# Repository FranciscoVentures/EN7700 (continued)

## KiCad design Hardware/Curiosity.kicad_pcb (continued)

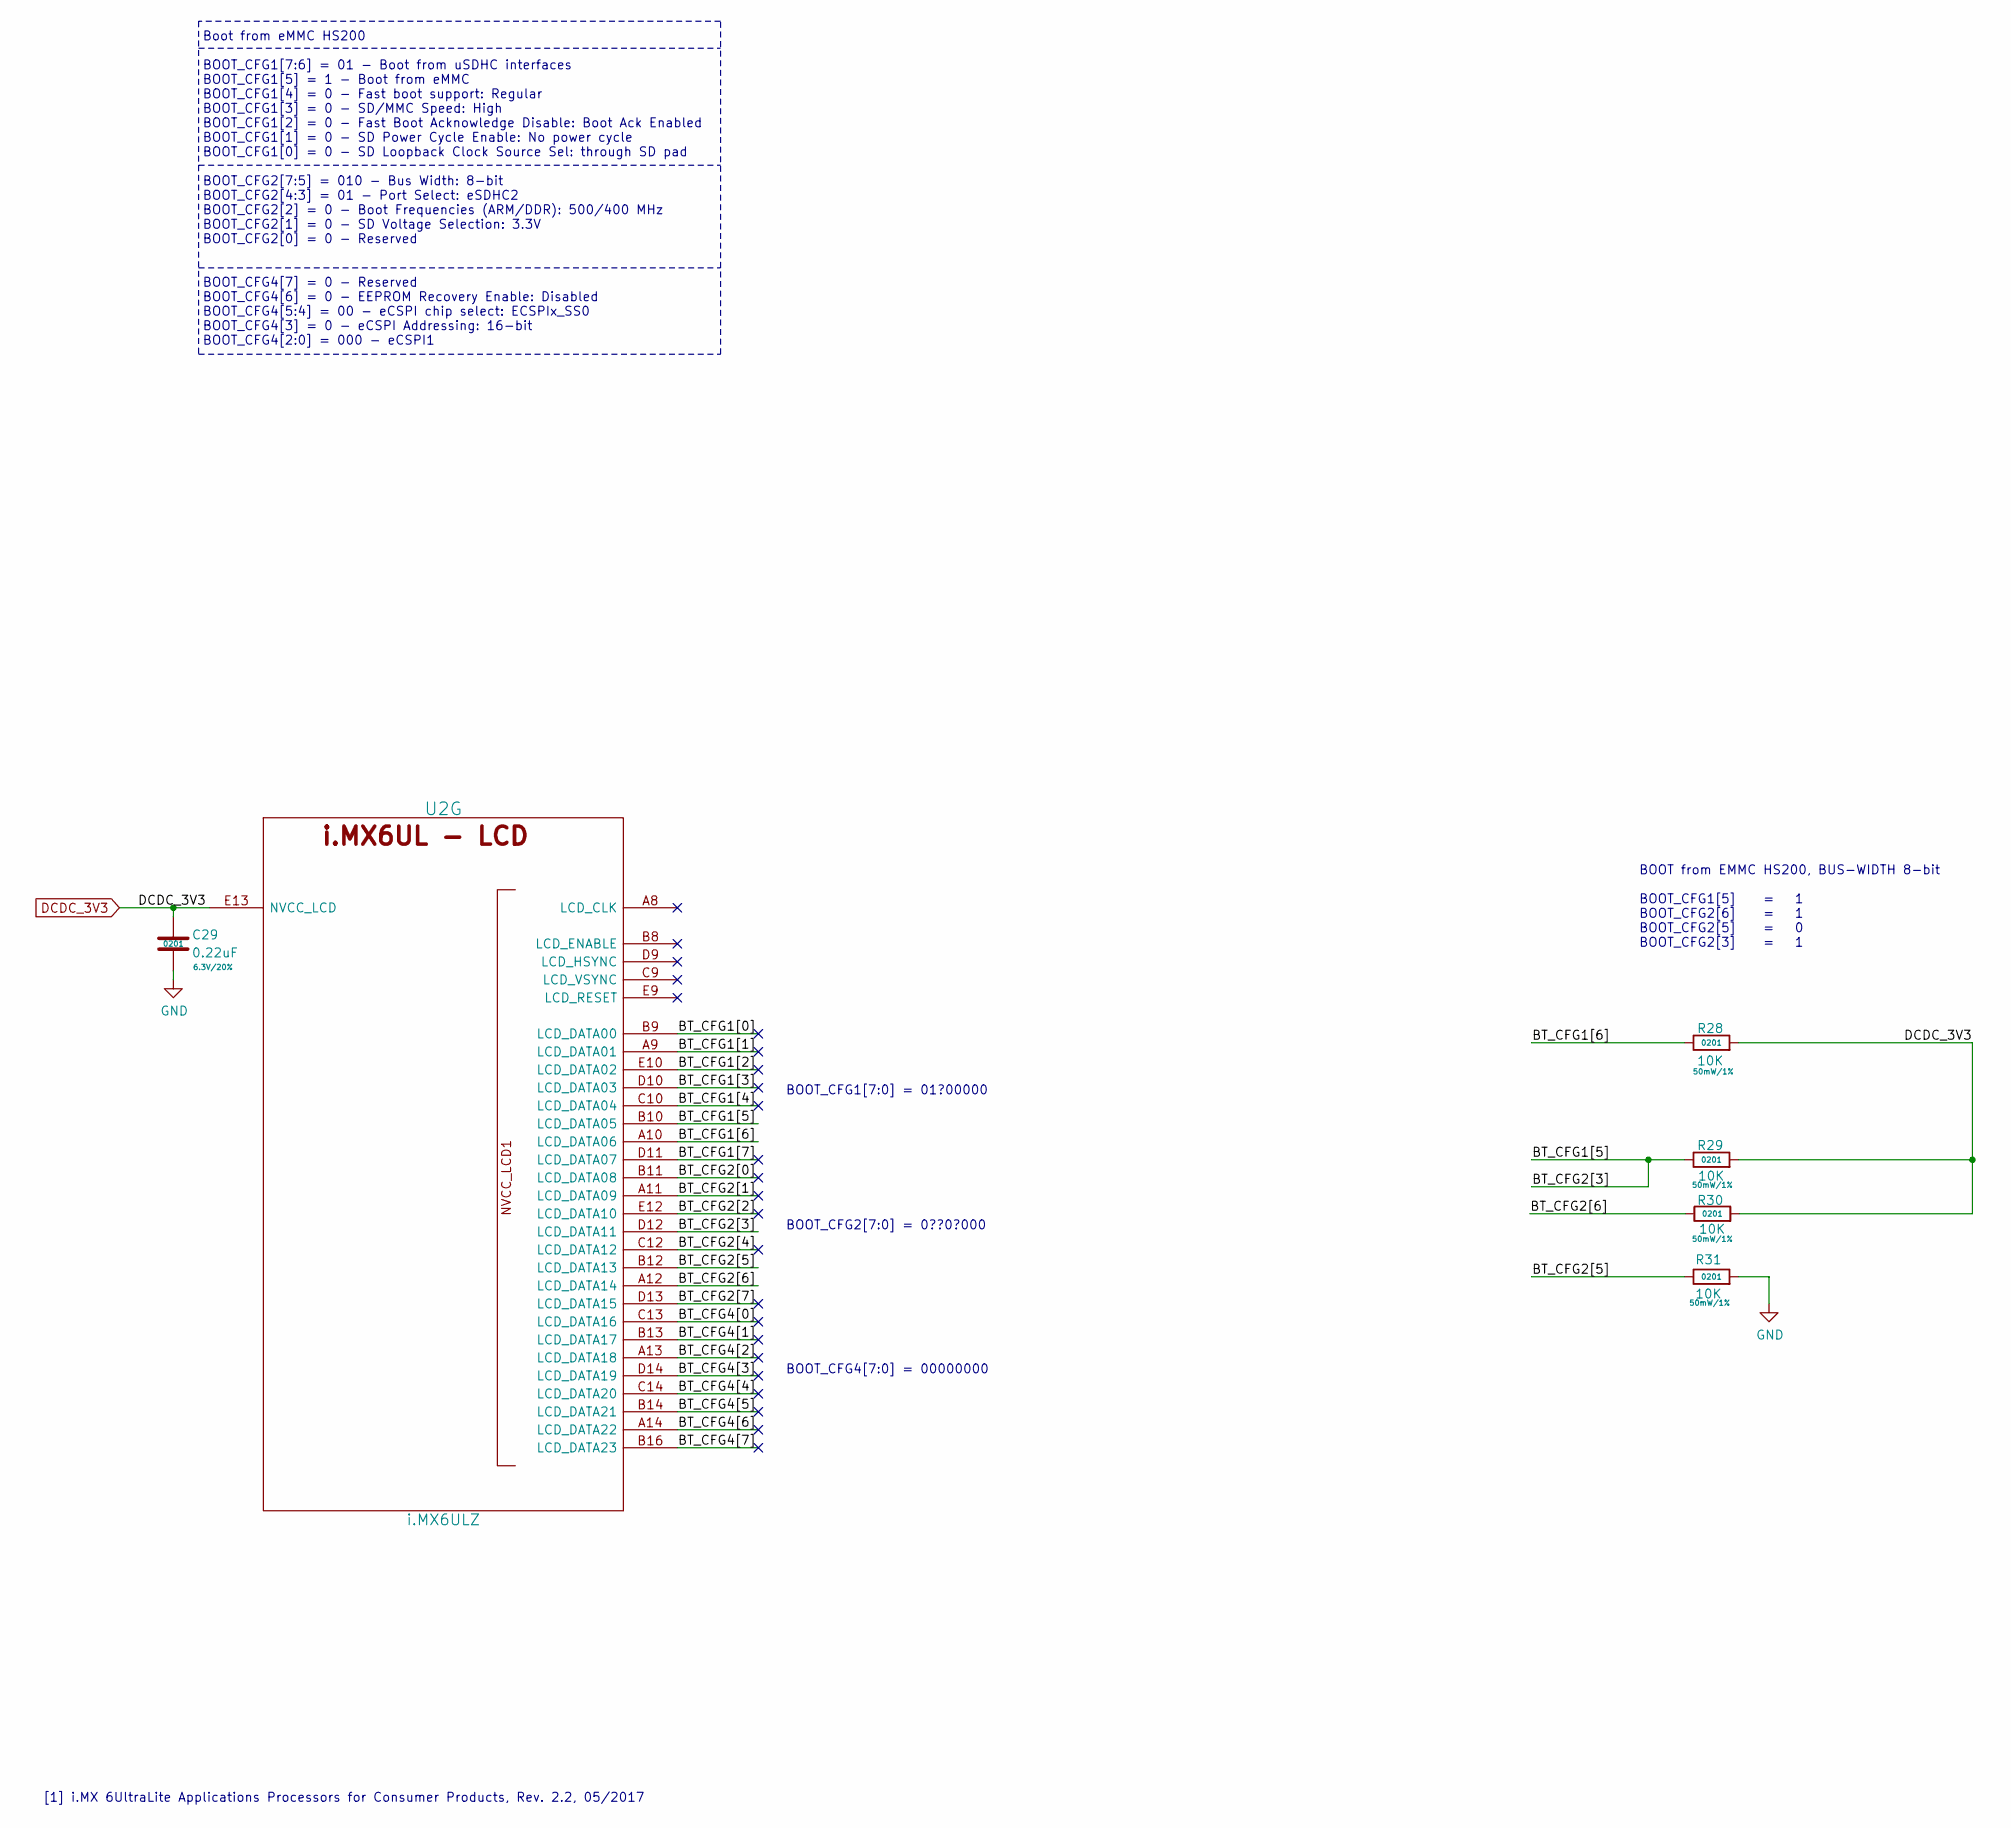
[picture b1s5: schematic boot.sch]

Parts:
C29: 0.22uF; SM0201; Rating 6.3V/20%; Mfg PN GRM033R60J224ME15D; Digi-Key_PN 490-10407-1-ND
R28, R29, R30, R31: 10K; R_0201_0603Metric; Rating 50mW/1%; Mfg PN CRCW020110K0JNED; Digi-Key_PN 541-10KAGCT-ND
U2: i.MX6ULZ; SOT1534-2; Mfg PN MCIMX6Z0DVM09AB; Digi-Key_PN 568-14726-ND

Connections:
/Boot/BT_CFG1[0]: U2.B9 (LCD_DATA00); also elsewhere on the board
/Boot/BT_CFG1[1]: U2.A9 (LCD_DATA01); also elsewhere on the board
/Boot/BT_CFG1[2]: U2.E10 (LCD_DATA02); also elsewhere on the board
/Boot/BT_CFG1[3]: U2.D10 (LCD_DATA03); also elsewhere on the board
/Boot/BT_CFG1[4]: U2.C10 (LCD_DATA04); also elsewhere on the board
/Boot/BT_CFG1[5]: R29.1, U2.B10 (LCD_DATA05), U2.D12 (LCD_DATA11); also elsewhere on the board
/Boot/BT_CFG1[6]: R28.1, U2.A10 (LCD_DATA06); also elsewhere on the board
/Boot/BT_CFG1[7]: U2.D11 (LCD_DATA07); also elsewhere on the board
/Boot/BT_CFG2[0]: U2.B11 (LCD_DATA08); also elsewhere on the board
/Boot/BT_CFG2[1]: U2.A11 (LCD_DATA09); also elsewhere on the board
/Boot/BT_CFG2[2]: U2.E12 (LCD_DATA10); also elsewhere on the board
/Boot/BT_CFG2[4]: U2.C12 (LCD_DATA12); also elsewhere on the board
/Boot/BT_CFG2[5]: R31.1, U2.B12 (LCD_DATA13); also elsewhere on the board
/Boot/BT_CFG2[6]: R30.1, U2.A12 (LCD_DATA14); also elsewhere on the board
/Boot/BT_CFG2[7]: U2.D13 (LCD_DATA15); also elsewhere on the board
/Boot/BT_CFG4[0]: U2.C13 (LCD_DATA16); also elsewhere on the board
/Boot/BT_CFG4[1]: U2.B13 (LCD_DATA17); also elsewhere on the board
/Boot/BT_CFG4[2]: U2.A13 (LCD_DATA18); also elsewhere on the board
/Boot/BT_CFG4[3]: U2.D14 (LCD_DATA19); also elsewhere on the board
/Boot/BT_CFG4[4]: U2.C14 (LCD_DATA20); also elsewhere on the board
/Boot/BT_CFG4[5]: U2.B14 (LCD_DATA21); also elsewhere on the board
/Boot/BT_CFG4[6]: U2.A14 (LCD_DATA22); also elsewhere on the board
/Boot/BT_CFG4[7]: U2.B16 (LCD_DATA23); also elsewhere on the board
DCDC_3V3: C29.1, R28.2, R29.2, R30.2, U2.E13 (NVCC_LCD); also elsewhere on the board
GND: C29.2, R31.2; also elsewhere on the board
unnamed 184: U2.A8 (LCD_CLK); also elsewhere on the board
unnamed 188: U2.B8 (LCD_ENABLE); also elsewhere on the board
unnamed 192: U2.C9 (LCD_VSYNC); also elsewhere on the board
unnamed 197: U2.D9 (LCD_HSYNC); also elsewhere on the board
unnamed 201: U2.E9 (LCD_RESET); also elsewhere on the board

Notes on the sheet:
Boot from eMMC HS200 BOOT_CFG1[7:6] = 01 - Boot from uSDHC interfaces BOOT_CFG1[5] = 1 - Boot from eMMC BOOT_CFG1[4] = 0 - Fast boot support: Regular BOOT_CFG1[3] = 0 - SD/MMC Speed: High BOOT_CFG1[2] = 0 - Fast Boot Acknowledge Disable: Boot Ack Enabled BOOT_CFG1[1] = 0 - SD Power Cycle Enable: No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
BOOT_CFG4[7:0] = 00000000
BOOT from EMMC HS200, BUS-WIDTH 8-bit BOOT_CFG1[5] = 1 BOOT_CFG2[6] = 1 BOOT_CFG2[5] = 0 BOOT_CFG2[3] = 1
BOOT_CFG2[7:0] = 0??0?000
BOOT_CFG1[7:0] = 01?00000
[1] i.MX 6UltraLite Applications Processors for Consumer Products, Rev. 2.2, 05/2017

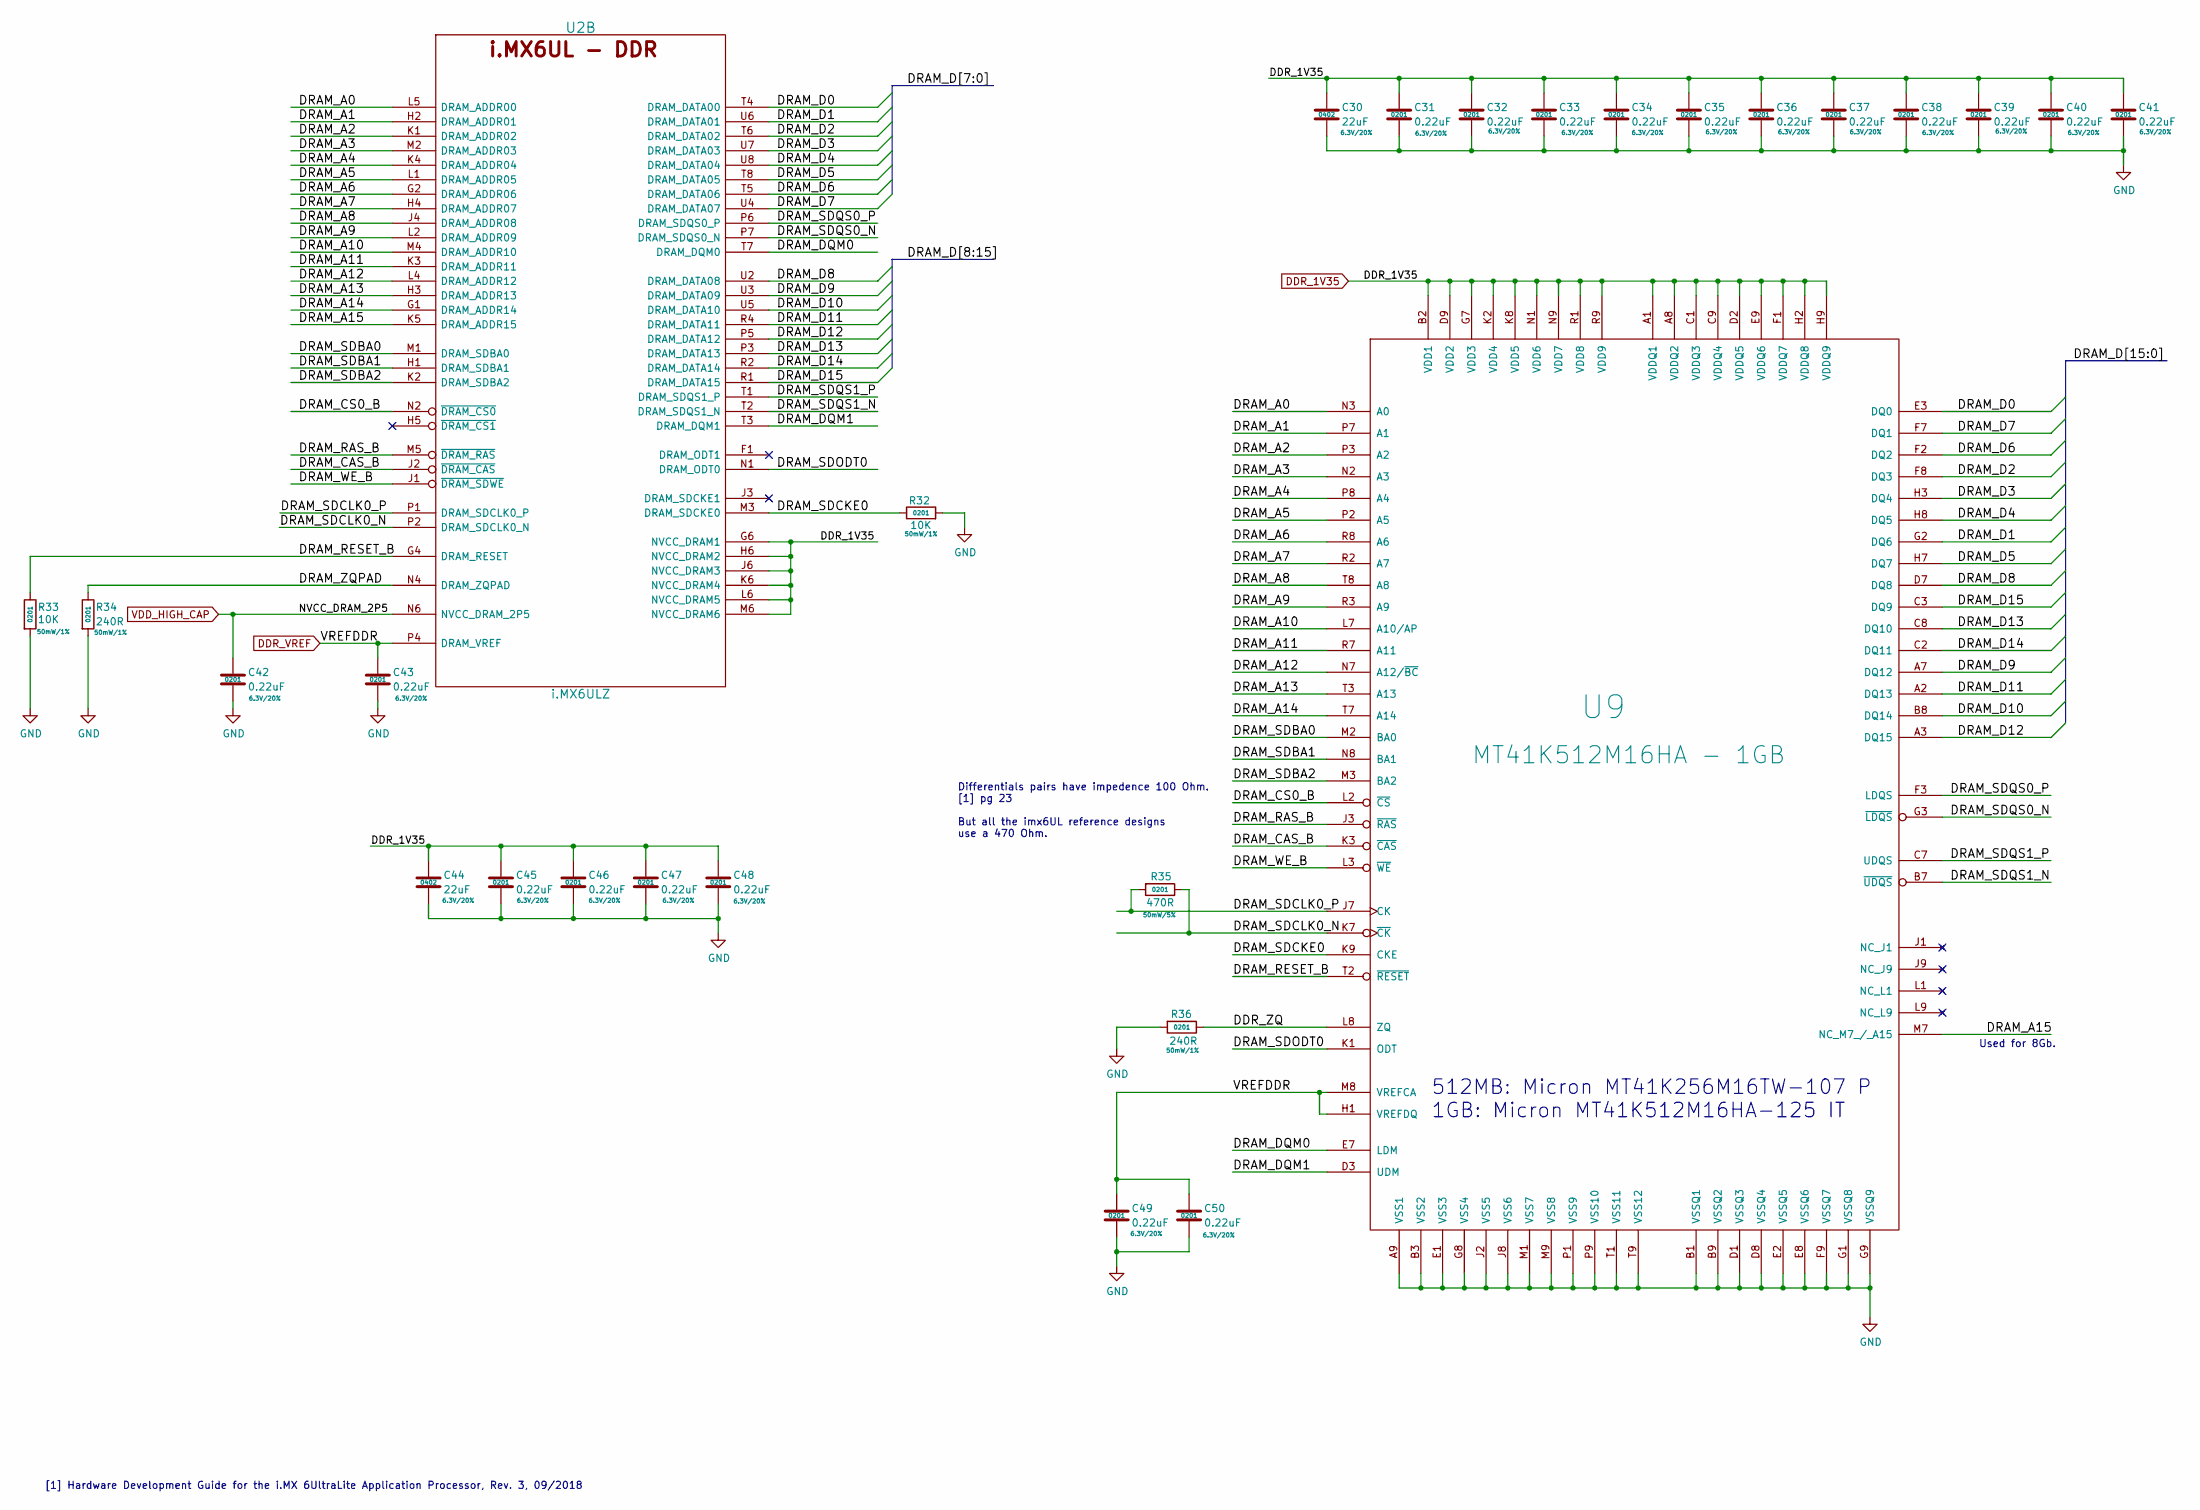
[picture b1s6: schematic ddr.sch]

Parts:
C30, C44: 22uF; SM0402; Rating 6.3V/20%; Mfg PN CL05A226MQ5N6J8; Digi-Key_PN 1276-7090-1-ND
C31, C32, C33, C34, C35, C36, C37, C38, C39, C40, C41, C42, C43, C45, C46, C47, C48, C49, C50: 0.22uF; SM0201; Rating 6.3V/20%; Mfg PN GRM033R60J224ME15D; Digi-Key_PN 490-10407-1-ND
R32, R33: 10K; R_0201_0603Metric; Rating 50mW/1%; Mfg PN CRCW020110K0JNED; Digi-Key_PN 541-10KAGCT-ND
R34, R36: 240R; R_0201_0603Metric; Rating 50mW/1%; Mfg PN CRCW0201240RFNED; Digi-Key_PN 541-2949-1-ND
R35: 470R; R_0201_0603Metric; Rating 50mW/5%; Mfg PN CRCW0201470RJNED; Digi-Key_PN 541-470AGCT-ND
U2: i.MX6ULZ; SOT1534-2; Mfg PN MCIMX6Z0DVM09AB; Digi-Key_PN 568-14726-ND
U9: MT41K512M16HA - 1GB; MICRON-FBGA-96; Mfg PN MT41K512M16HA-125 IT:A; Digi-Key_PN MT41K512M16HA-125IT:A-ND

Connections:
/DDR/DDR_ZQ: R36.1, U9.L8 (ZQ)
/DDR/DRAM_A0: U2.L5 (DRAM_ADDR00), U9.N3 (A0); also elsewhere on the board
/DDR/DRAM_A1: U2.H2 (DRAM_ADDR01), U9.P7 (A1); also elsewhere on the board
/DDR/DRAM_A2: U2.K1 (DRAM_ADDR02), U9.P3 (A2); also elsewhere on the board
/DDR/DRAM_A3: U2.M2 (DRAM_ADDR03), U9.N2 (A3); also elsewhere on the board
/DDR/DRAM_A4: U2.K4 (DRAM_ADDR04), U9.P8 (A4); also elsewhere on the board
/DDR/DRAM_A5: U2.L1 (DRAM_ADDR05), U9.P2 (A5); also elsewhere on the board
/DDR/DRAM_A6: U2.G2 (DRAM_ADDR06), U9.R8 (A6); also elsewhere on the board
/DDR/DRAM_A7: U2.H4 (DRAM_ADDR07), U9.R2 (A7); also elsewhere on the board
/DDR/DRAM_A8: U2.J4 (DRAM_ADDR08), U9.T8 (A8); also elsewhere on the board
/DDR/DRAM_A9: U2.L2 (DRAM_ADDR09), U9.R3 (A9); also elsewhere on the board
/DDR/DRAM_A10: U2.M4 (DRAM_ADDR10), U9.L7 (A10/AP); also elsewhere on the board
/DDR/DRAM_A11: U2.K3 (DRAM_ADDR11), U9.R7 (A11); also elsewhere on the board
/DDR/DRAM_A12: U2.L4 (DRAM_ADDR12), U9.N7 (A12/~BC); also elsewhere on the board
/DDR/DRAM_A13: U2.H3 (DRAM_ADDR13), U9.T3 (A13); also elsewhere on the board
/DDR/DRAM_A14: U2.G1 (DRAM_ADDR14), U9.T7 (A14); also elsewhere on the board
/DDR/DRAM_A15: U2.K5 (DRAM_ADDR15), U9.M7 (NC_M7_/_A15); also elsewhere on the board
/DDR/DRAM_CAS_B: U2.J2 (~DRAM_CAS), U9.K3 (~CAS); also elsewhere on the board
/DDR/DRAM_CS0_B: U2.N2 (~DRAM_CS0), U9.L2 (~CS); also elsewhere on the board
/DDR/DRAM_D0: U2.T4 (DRAM_DATA00), U9.E3 (DQ0); also elsewhere on the board
/DDR/DRAM_D1: U2.U6 (DRAM_DATA01), U9.G2 (DQ6); also elsewhere on the board
/DDR/DRAM_D2: U2.T6 (DRAM_DATA02), U9.F8 (DQ3); also elsewhere on the board
/DDR/DRAM_D3: U2.U7 (DRAM_DATA03), U9.H3 (DQ4); also elsewhere on the board
/DDR/DRAM_D4: U2.U8 (DRAM_DATA04), U9.H8 (DQ5); also elsewhere on the board
/DDR/DRAM_D5: U2.T8 (DRAM_DATA05), U9.H7 (DQ7); also elsewhere on the board
/DDR/DRAM_D6: U2.T5 (DRAM_DATA06), U9.F2 (DQ2); also elsewhere on the board
/DDR/DRAM_D7: U2.U4 (DRAM_DATA07), U9.F7 (DQ1); also elsewhere on the board
/DDR/DRAM_D8: U2.U2 (DRAM_DATA08), U9.D7 (DQ8); also elsewhere on the board
/DDR/DRAM_D9: U2.U3 (DRAM_DATA09), U9.A7 (DQ12); also elsewhere on the board
/DDR/DRAM_D10: U2.U5 (DRAM_DATA10), U9.B8 (DQ14); also elsewhere on the board
/DDR/DRAM_D11: U2.R4 (DRAM_DATA11), U9.A2 (DQ13); also elsewhere on the board
/DDR/DRAM_D12: U2.P5 (DRAM_DATA12), U9.A3 (DQ15); also elsewhere on the board
/DDR/DRAM_D13: U2.P3 (DRAM_DATA13), U9.C8 (DQ10); also elsewhere on the board
/DDR/DRAM_D14: U2.R2 (DRAM_DATA14), U9.C2 (DQ11); also elsewhere on the board
/DDR/DRAM_D15: U2.R1 (DRAM_DATA15), U9.C3 (DQ9); also elsewhere on the board
/DDR/DRAM_DQM0: U2.T7 (DRAM_DQM0), U9.E7 (LDM); also elsewhere on the board
/DDR/DRAM_DQM1: U2.T3 (DRAM_DQM1), U9.D3 (UDM); also elsewhere on the board
/DDR/DRAM_RAS_B: U2.M5 (~DRAM_RAS), U9.J3 (~RAS); also elsewhere on the board
/DDR/DRAM_RESET_B: R33.1, U2.G4 (DRAM_RESET), U9.T2 (~RESET); also elsewhere on the board
/DDR/DRAM_SDBA0: U2.M1 (DRAM_SDBA0), U9.M2 (BA0); also elsewhere on the board
/DDR/DRAM_SDBA1: U2.H1 (DRAM_SDBA1), U9.N8 (BA1); also elsewhere on the board
/DDR/DRAM_SDBA2: U2.K2 (DRAM_SDBA2), U9.M3 (BA2); also elsewhere on the board
/DDR/DRAM_SDCKE0: R32.1, U2.M3 (DRAM_SDCKE0), U9.K9 (CKE); also elsewhere on the board
/DDR/DRAM_SDCLK0_N: R35.1, U2.P2 (DRAM_SDCLK0_N), U9.K7 (~CK); also elsewhere on the board
/DDR/DRAM_SDCLK0_P: R35.2, U2.P1 (DRAM_SDCLK0_P), U9.J7 (CK); also elsewhere on the board
/DDR/DRAM_SDODT0: U2.N1 (DRAM_ODT0), U9.K1 (ODT); also elsewhere on the board
/DDR/DRAM_SDQS0_N: U2.P7 (DRAM_SDQS0_N), U9.G3 (~LDQS); also elsewhere on the board
/DDR/DRAM_SDQS0_P: U2.P6 (DRAM_SDQS0_P), U9.F3 (LDQS); also elsewhere on the board
/DDR/DRAM_SDQS1_N: U2.T2 (DRAM_SDQS1_N), U9.B7 (~UDQS); also elsewhere on the board
/DDR/DRAM_SDQS1_P: U2.T1 (DRAM_SDQS1_P), U9.C7 (UDQS); also elsewhere on the board
/DDR/DRAM_WE_B: U2.J1 (~DRAM_SDWE), U9.L3 (~WE); also elsewhere on the board
/DDR/DRAM_ZQPAD: R34.1, U2.N4 (DRAM_ZQPAD); also elsewhere on the board
DDR_1V35: C30.1, C31.1, C32.1, C33.1, C34.1, C35.1, C36.1, C37.1, C38.1, C39.1, C40.1, C41.1, C44.1, C45.1, C46.1, C47.1, C48.1, U2.G6 (NVCC_DRAM1), U2.H6 (NVCC_DRAM2), U2.J6 (NVCC_DRAM3), U2.K6 (NVCC_DRAM4), U2.L6 (NVCC_DRAM5), U2.M6 (NVCC_DRAM6), U9.A1 (VDDQ1), U9.A8 (VDDQ2), U9.B2 (VDD1), U9.C1 (VDDQ3), U9.C9 (VDDQ4), U9.D2 (VDDQ5), U9.D9 (VDD2), U9.E9 (VDDQ6), U9.F1 (VDDQ7), U9.G7 (VDD3), U9.H2 (VDDQ8), U9.H9 (VDDQ9), U9.K2 (VDD4), U9.K8 (VDD5), U9.N1 (VDD6), U9.N9 (VDD7), U9.R1 (VDD8), U9.R9 (VDD9); also elsewhere on the board
DDR_VREF: C43.1, C49.1, C50.1, U2.P4 (DRAM_VREF), U9.H1 (VREFDQ), U9.M8 (VREFCA); also elsewhere on the board
GND: C30.2, C31.2, C32.2, C33.2, C34.2, C35.2, C36.2, C37.2, C38.2, C39.2, C40.2, C41.2, C42.2, C43.2, C44.2, C45.2, C46.2, C47.2, C48.2, C49.2, C50.2, R32.2, R33.2, R34.2, R36.2, U9.A9 (VSS1), U9.B1 (VSSQ1), U9.B3 (VSS2), U9.B9 (VSSQ2), U9.D1 (VSSQ3), U9.D8 (VSSQ4), U9.E1 (VSS3), U9.E2 (VSSQ5), U9.E8 (VSSQ6), U9.F9 (VSSQ7), U9.G1 (VSSQ8), U9.G8 (VSS4), U9.G9 (VSSQ9), U9.J2 (VSS5), U9.J8 (VSS6), U9.M1 (VSS7), U9.M9 (VSS8), U9.P1 (VSS9), U9.P9 (VSS10), U9.T1 (VSS11), U9.T9 (VSS12); also elsewhere on the board
unnamed 206: U2.F1 (DRAM_ODT1); also elsewhere on the board
unnamed 212: U2.H5 (~DRAM_CS1); also elsewhere on the board
unnamed 214: U2.J3 (DRAM_SDCKE1); also elsewhere on the board
VDD_HIGH_CAP: C42.1, U2.N6 (NVCC_DRAM_2P5); also elsewhere on the board

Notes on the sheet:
Used for 8Gb.
512MB: Micron MT41K256M16TW-107 P 1GB: Micron MT41K512M16HA-125 IT
[1] Hardware Development Guide for the i.MX 6UltraLite Application Processor, Rev. 3, 09/2018
Differentials pairs have impedence 100 Ohm. [1] pg 23 But all the imx6UL reference designs use a 470 Ohm.

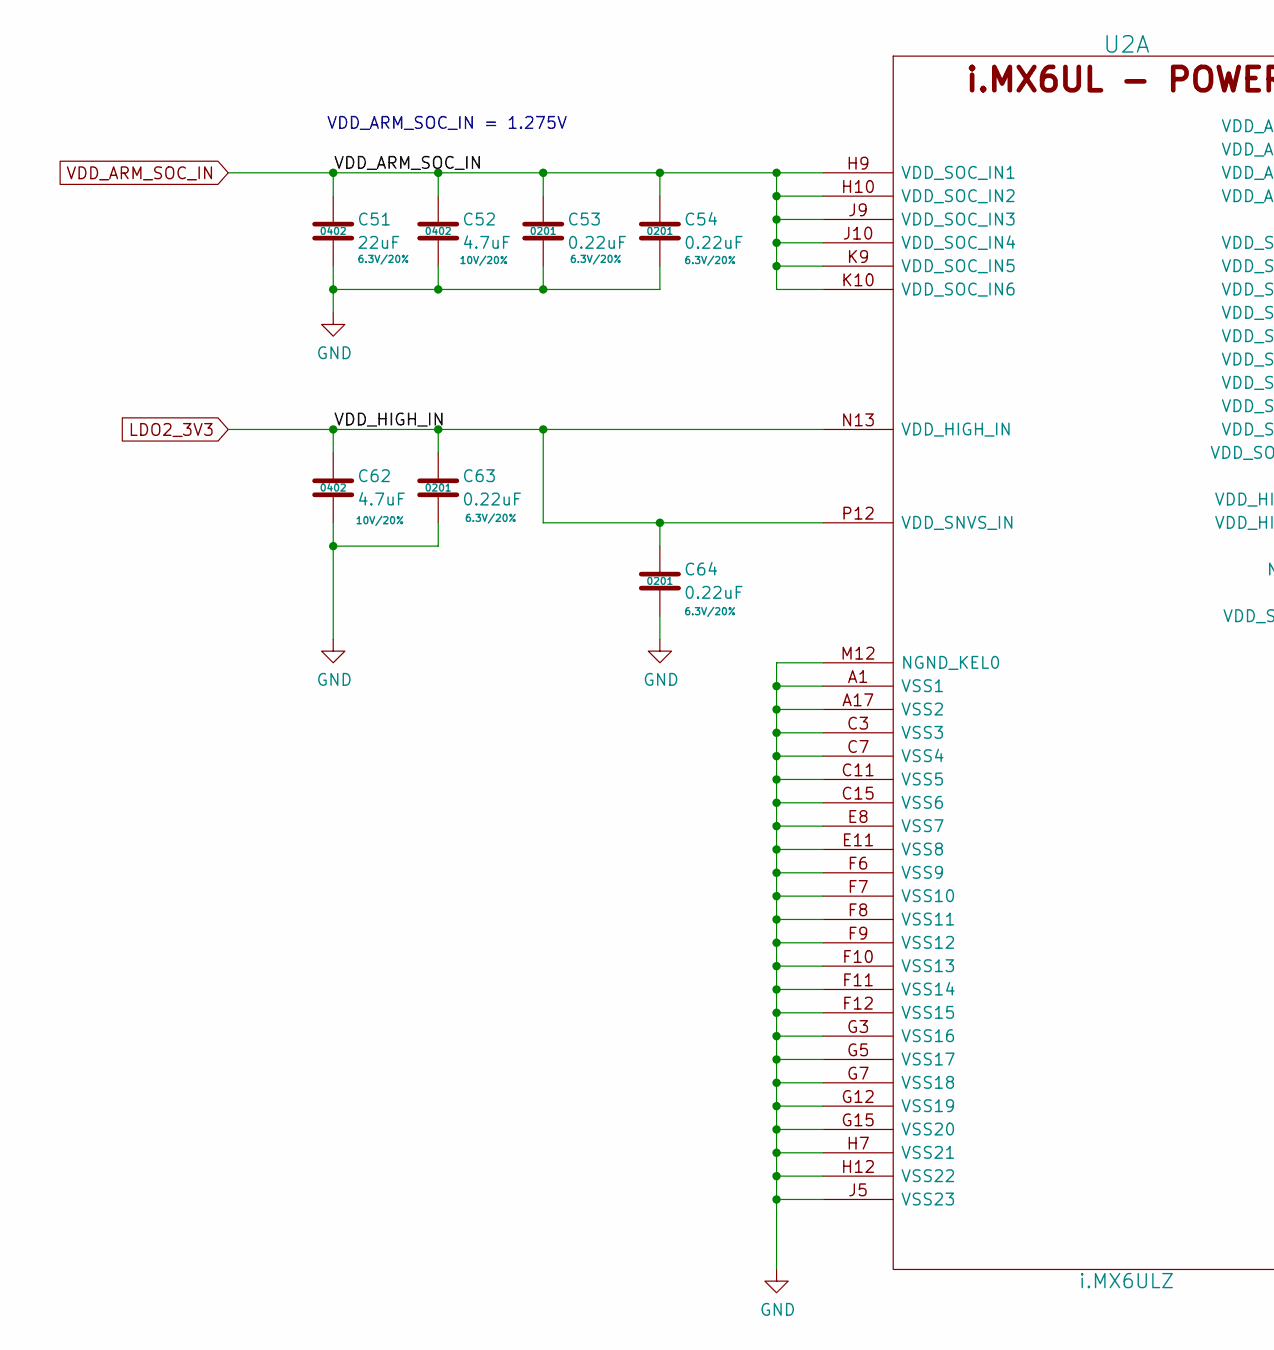
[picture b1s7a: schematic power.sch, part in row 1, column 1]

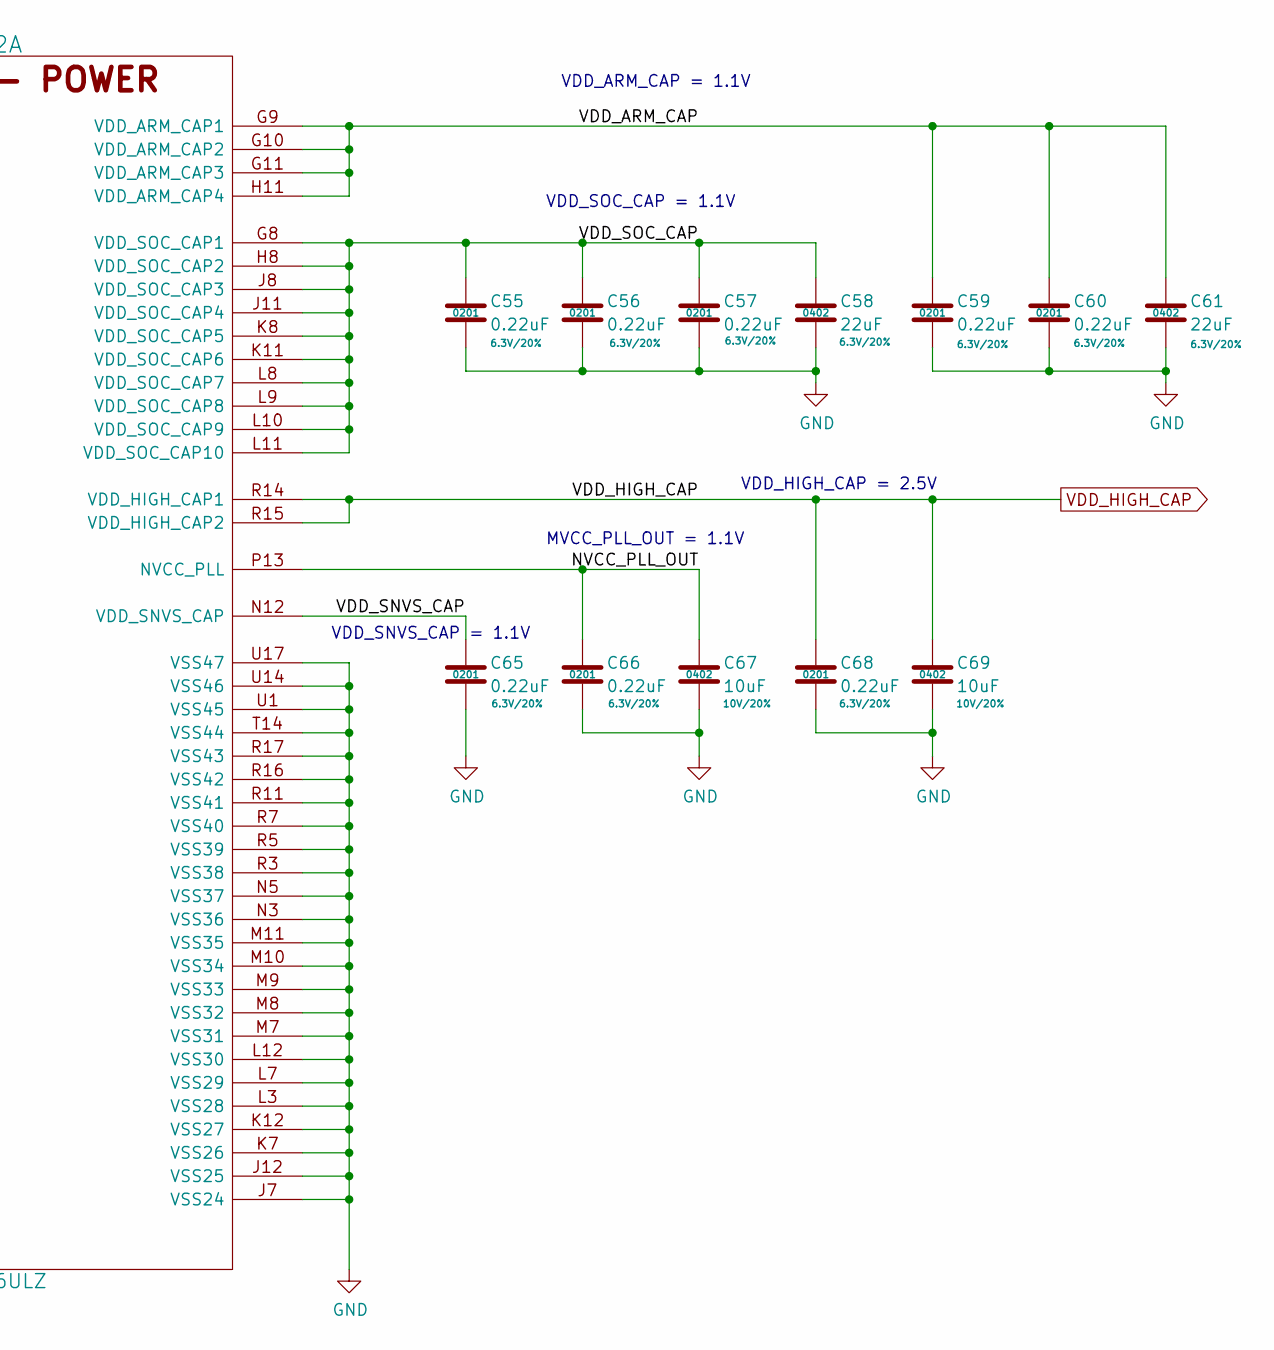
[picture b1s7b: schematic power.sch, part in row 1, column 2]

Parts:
C51, C58, C61: 22uF; SM0402; Rating 6.3V/20%; Mfg PN CL05A226MQ5N6J8; Digi-Key_PN 1276-7090-1-ND
C52, C62: 4.7uF; SM0402; Rating 10V/20%; Mfg PN ZRB15XR61A475ME01D; Digi-Key_PN 490-10984-1-ND
C53, C54, C55, C56, C57, C59, C60, C63, C64, C65, C66, C68: 0.22uF; SM0201; Rating 6.3V/20%; Mfg PN GRM033R60J224ME15D; Digi-Key_PN 490-10407-1-ND
C67, C69: 10uF; SM0402; Rating 10V/20%; Mfg PN CL05A106MP8NUB8; Digi-Key_PN 1276-6830-1-ND
U2: i.MX6ULZ; SOT1534-2; Mfg PN MCIMX6Z0DVM09AB; Digi-Key_PN 568-14726-ND

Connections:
/Power/NVCC_PLL_OUT: C66.1, C67.1, U2.P13 (NVCC_PLL); also elsewhere on the board
/Power/VDD_ARM_CAP: C59.1, C60.1, C61.1, U2.G9 (VDD_ARM_CAP1), U2.G10 (VDD_ARM_CAP2), U2.G11 (VDD_ARM_CAP3), U2.H11 (VDD_ARM_CAP4); also elsewhere on the board
/Power/VDD_SNVS_CAP: C65.1, U2.N12 (VDD_SNVS_CAP); also elsewhere on the board
/Power/VDD_SOC_CAP: C55.1, C56.1, C57.1, C58.1, U2.G8 (VDD_SOC_CAP1), U2.H8 (VDD_SOC_CAP2), U2.J8 (VDD_SOC_CAP3), U2.J11 (VDD_SOC_CAP4), U2.K8 (VDD_SOC_CAP5), U2.K11 (VDD_SOC_CAP6), U2.L8 (VDD_SOC_CAP7), U2.L9 (VDD_SOC_CAP8), U2.L10 (VDD_SOC_CAP9), U2.L11 (VDD_SOC_CAP10); also elsewhere on the board
GND: C51.2, C52.2, C53.2, C54.2, C55.2, C56.2, C57.2, C58.2, C59.2, C60.2, C61.2, C62.2, C63.2, C64.2, C65.2, C66.2, C67.2, C68.2, C69.2, U2.A1 (VSS1), U2.A17 (VSS2), U2.C3 (VSS3), U2.C7 (VSS4), U2.C11 (VSS5), U2.C15 (VSS6), U2.E8 (VSS7), U2.E11 (VSS8), U2.F6 (VSS9), U2.F7 (VSS10), U2.F8 (VSS11), U2.F9 (VSS12), U2.F10 (VSS13), U2.F11 (VSS14), U2.F12 (VSS15), U2.G3 (VSS16), U2.G5 (VSS17), U2.G7 (VSS18), U2.G12 (VSS19), U2.G15 (VSS20), U2.H7 (VSS21), U2.H12 (VSS22), U2.J5 (VSS23), U2.J7 (VSS24), U2.J12 (VSS25), U2.K7 (VSS26), U2.K12 (VSS27), U2.L3 (VSS28), U2.L7 (VSS29), U2.L12 (VSS30), U2.M7 (VSS31), U2.M8 (VSS32), U2.M9 (VSS33), U2.M10 (VSS34), U2.M11 (VSS35), U2.M12 (NGND_KEL0), U2.N3 (VSS36), U2.N5 (VSS37), U2.R3 (VSS38), U2.R5 (VSS39), U2.R7 (VSS40), U2.R11 (VSS41), U2.R16 (VSS42), U2.R17 (VSS43), U2.T14 (VSS44), U2.U1 (VSS45), U2.U14 (VSS46), U2.U17 (VSS47); also elsewhere on the board
LDO2_3V3: C62.1, C63.1, C64.1, U2.N13 (VDD_HIGH_IN), U2.P12 (VDD_SNVS_IN); also elsewhere on the board
VDD_ARM_SOC_IN: C51.1, C52.1, C53.1, C54.1, U2.H9 (VDD_SOC_IN1), U2.H10 (VDD_SOC_IN2), U2.J9 (VDD_SOC_IN3), U2.J10 (VDD_SOC_IN4), U2.K9 (VDD_SOC_IN5), U2.K10 (VDD_SOC_IN6); also elsewhere on the board
VDD_HIGH_CAP: C68.1, C69.1, U2.R14 (VDD_HIGH_CAP1), U2.R15 (VDD_HIGH_CAP2); also elsewhere on the board

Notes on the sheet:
VDD_ARM_SOC_IN = 1.275V
VDD_ARM_CAP = 1.1V
VDD_SOC_CAP = 1.1V
VDD_HIGH_CAP = 2.5V
MVCC_PLL_OUT = 1.1V
VDD_SNVS_CAP = 1.1V

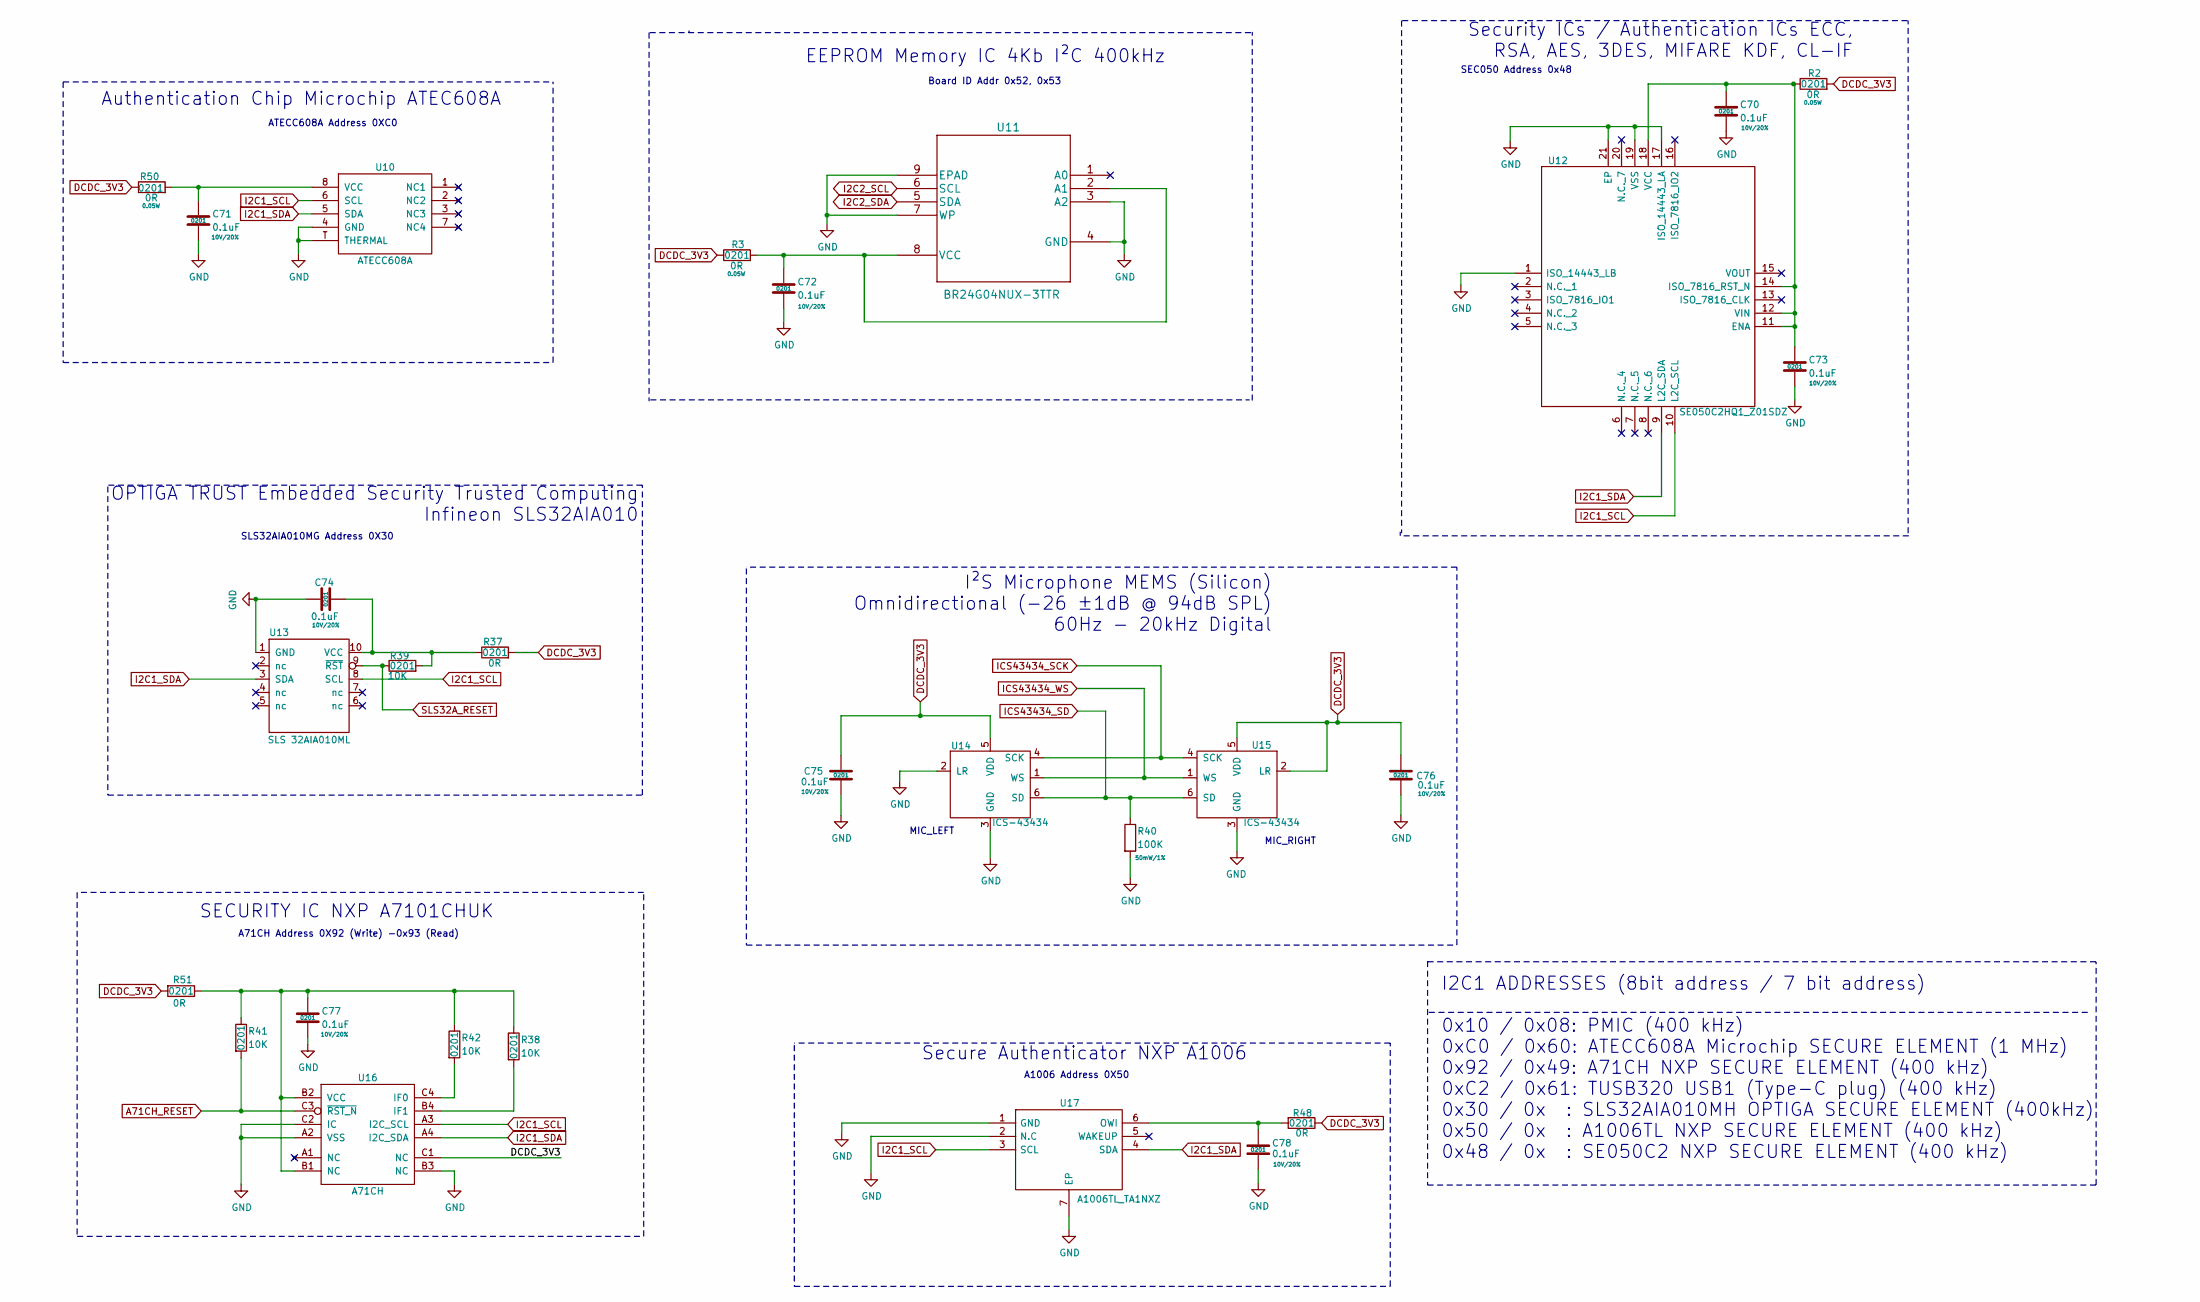
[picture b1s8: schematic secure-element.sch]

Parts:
C70, C71, C72, C73, C74, C75, C76, C77, C78: 0.1uF; SM0201; Rating 10V/20%; Mfg PN GRM033R61A104ME15D; Digi-Key_PN 490-5405-1-ND
R2, R3, R37, R50: 0R; R_0201_0603Metric; Rating 0.05W; Mfg PN CRCW02010000Z0ED; Digi-Key_PN 541-0.0AGCT-ND
R38, R39, R41, R42: 10K; R_0201_0603Metric; Rating 50mW/1%; Mfg PN CRCW020110K0JNED; Digi-Key_PN 541-10KAGCT-ND
R40: 100K; R_0201_0603Metric; Rating 50mW/1%; Mfg PN CRCW0201100KJNED; Digi-Key_PN 541-100KAGCT-ND
R48, R51: 0R; R_0201_0603Metric; Rating 50mW/1%; Mfg PN CRCW020110K0JNED; Digi-Key_PN 541-10KAGCT-ND
U10: ATECC608A; UDFN-8; Mfg PN ATECC608A-MAHDA; Digi-Key_PN ATECC608A-MAHDA-SCT-ND
U11: BR24G04NUX-3TTR; VSON008X2030_ROM; Mfg PN BR24G04NUX-3TTR; Digi-Key_PN BR24G04NUX-3TCT-ND
U12: SE050C2HQ1_Z01SDZ; QFN40P300X300X33-21N-D; Mfg PN SE050C2HQ1/Z01SDZ; Digi-Key_PN 568-15378-1-ND
U13: SLS 32AIA010ML; SLS; Mfg PN SLS32AIA010MH
U14, U15: ICS-43434; ICS43434; Mfg PN ICS-43434; Digi-Key_PN 1428-1066-1-ND
U16: A71CH; SOT1999-1; Mfg PN A7101CHUK/T0BC2HAZ; Digi-Key_PN 568-14698-1-ND
U17: A1006TL_TA1NXZ; SON65P200X200X50-7N; Mfg PN A1006TL/TA1NXZ; Digi-Key_PN 568-13635-1-ND

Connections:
A71CH_RESET: R41.2, U16.C3 (~RST_N); also elsewhere on the board
DCDC_3V3: C75.2, C76.2, R2.2, R3.1, R37.2, R48.1, R50.1, R51.2, U14.5 (VDD), U15.2 (LR), U15.5 (VDD), U16.C1 (NC); also elsewhere on the board
GND: C70.2, C71.2, C72.2, C73.2, C74.1, C75.1, C76.1, C77.2, C78.2, R40.2, U10.4 (GND), U10.T (THERMAL), U11.3 (A2), U11.4 (GND), U11.7 (WP), U11.9 (EPAD), U12.1 (ISO_14443_LB), U12.17 (ISO_14443_LA), U12.19 (VSS), U12.21 (EP), U13.1 (GND), U14.2 (LR), U14.3 (GND), U15.3 (GND), U16.A2 (VSS), U16.B3 (NC), U16.C2 (IC), U17.1 (GND), U17.2 (N.C), U17.7 (EP); also elsewhere on the board
I2C1_SCL: U10.6 (SCL), U12.10 (L2C_SCL), U13.8 (SCL), U16.A3 (I2C_SCL), U17.3 (SCL); also elsewhere on the board
I2C1_SDA: U10.5 (SDA), U12.9 (L2C_SDA), U13.3 (SDA), U16.A4 (I2C_SDA), U17.4 (SDA); also elsewhere on the board
I2C2_SCL: U11.6 (SCL); also elsewhere on the board
I2C2_SDA: U11.5 (SDA); also elsewhere on the board
ICS43434_SCK: U14.4 (SCK), U15.4 (SCK); also elsewhere on the board
ICS43434_SD: R40.1, U14.6 (SD), U15.6 (SD); also elsewhere on the board
ICS43434_WS: U14.1 (WS), U15.1 (WS); also elsewhere on the board
unnamed: C70.1, C73.1, R2.1, U12.11 (ENA), U12.12 (VIN), U12.14 (ISO_7816_RST_N), U12.18 (VCC)
unnamed: C71.1, R50.2, U10.8 (VCC)
unnamed: C72.1, R3.2, U11.2 (A1), U11.8 (VCC)
unnamed: C74.2, R37.1, R39.2, U13.10 (VCC)
unnamed: C77.1, R38.1, R41.1, R42.1, R51.1, U16.B1 (NC), U16.B2 (VCC)
unnamed: C78.1, R48.2, U17.6 (OWI)
unnamed: R38.2, U16.B4 (IF1)
unnamed: R42.2, U16.C4 (IF0)
SLS32A_RESET: R39.1, U13.9 (~RST); also elsewhere on the board

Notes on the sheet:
SLS32AIA010MG Address 0X30
A71CH Address 0X92 (Write) -0x93 (Read)
ATECC608A Address 0XC0
A1006 Address 0X50
SEC050 Address 0x48
Board ID Addr 0x52, 0x53
I2C1 ADDRESSES (8bit address / 7 bit address) 0x10 / 0x08: PMIC (400 kHz) 0xC0 / 0x60: ATECC608A Microchip SECURE ELEMENT (1 MHz) 0x92 / 0x49: A71CH NXP SECURE ELEMENT (400 kHz) 0xC2 / 0x61: TUSB320 USB1 (Type-C plug) (400 kHz) 0x30 / 0x : SLS32AIA010MH OPTIGA SECURE ELEMENT (400kHz) 0x50 / 0x : A1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
Secure Authenticator NXP A1006
I²S Microphone MEMS (Silicon) Omnidirectional (-26 ±1dB @ 94dB SPL) 60Hz - 20kHz Digital
Security ICs / Authentication ICs ECC, RSA, AES, 3DES, MIFARE KDF, CL-IF
EEPROM Memory IC 4Kb I²C 400kHz
OPTIGA TRUST Embedded Security Trusted Computing Infineon SLS32AIA010
SECURITY IC NXP A7101CHUK
Authentication Chip Microchip ATEC608A
MIC_RIGHT
MIC_LEFT

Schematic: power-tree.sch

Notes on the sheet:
USB1_VBUS
i.MX6ULZ
NVCC_ENET
VDD_SOC_IN
VDD_HIGH_IN
VDD_SNVS_IN
USB_OTG1_VBUS
VDDA_ADC_3P3
NVCC_GPIO
NVCC_CSI
NVCC_NAND
NVCC_SD1
NVCC_LCD
NVCC_UART
USB_OTG2_VBUS
NVCC_DRAM
NVCC_DRAM_2P5
VIN
Type-C port controller
TUSB320 - PLUG
GPS Module
u-blox ZOE-M8Q-0-10 GPS
TDK ICS-43434
Microphone MEMS
DDR3L 1GB/512MB
DDR
Microchip ATECC608A
Secure Element 1
A10
A11
A12
B12
B11
B10
GND
TX1+
TX1-
VBUS
CC1
SBU1
